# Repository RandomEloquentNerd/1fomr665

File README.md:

# 1form65
These are the design files for my new 65% keyboard PCB, I use Eagle and AutoCAD for designing. 
A few things  before I proceed; as apparent it's in a very crude state currently and needs a lot of tinkering, since this is my first design, I ran into quite a few problems;
1. The board became a tad too crowded, so I made a bit of space on the left for all the electronics to rest, this might make trouble for routing later, but I'm not sure.
2. Since I'll be hand soldering all of the components myself, I went for larger, through hole ones, instead of the usual SMD business. Fitting everything on the board has been a rather nerve wracking affair, but let me know what you think. 
3. Connecting the controller to the matrix. Now this is where I have faltered. Connecting the rows to the controller was straightforward enough, albeit when it comes to connecting columns, the airwire ends up either one key switch down from where I intended (the top pin of the top switch) or on the bottom switch. I figured that the way I had routed the column initially, but on redoing it multiple times, the problem still persists, so I'm uncerrtain how to proceed.

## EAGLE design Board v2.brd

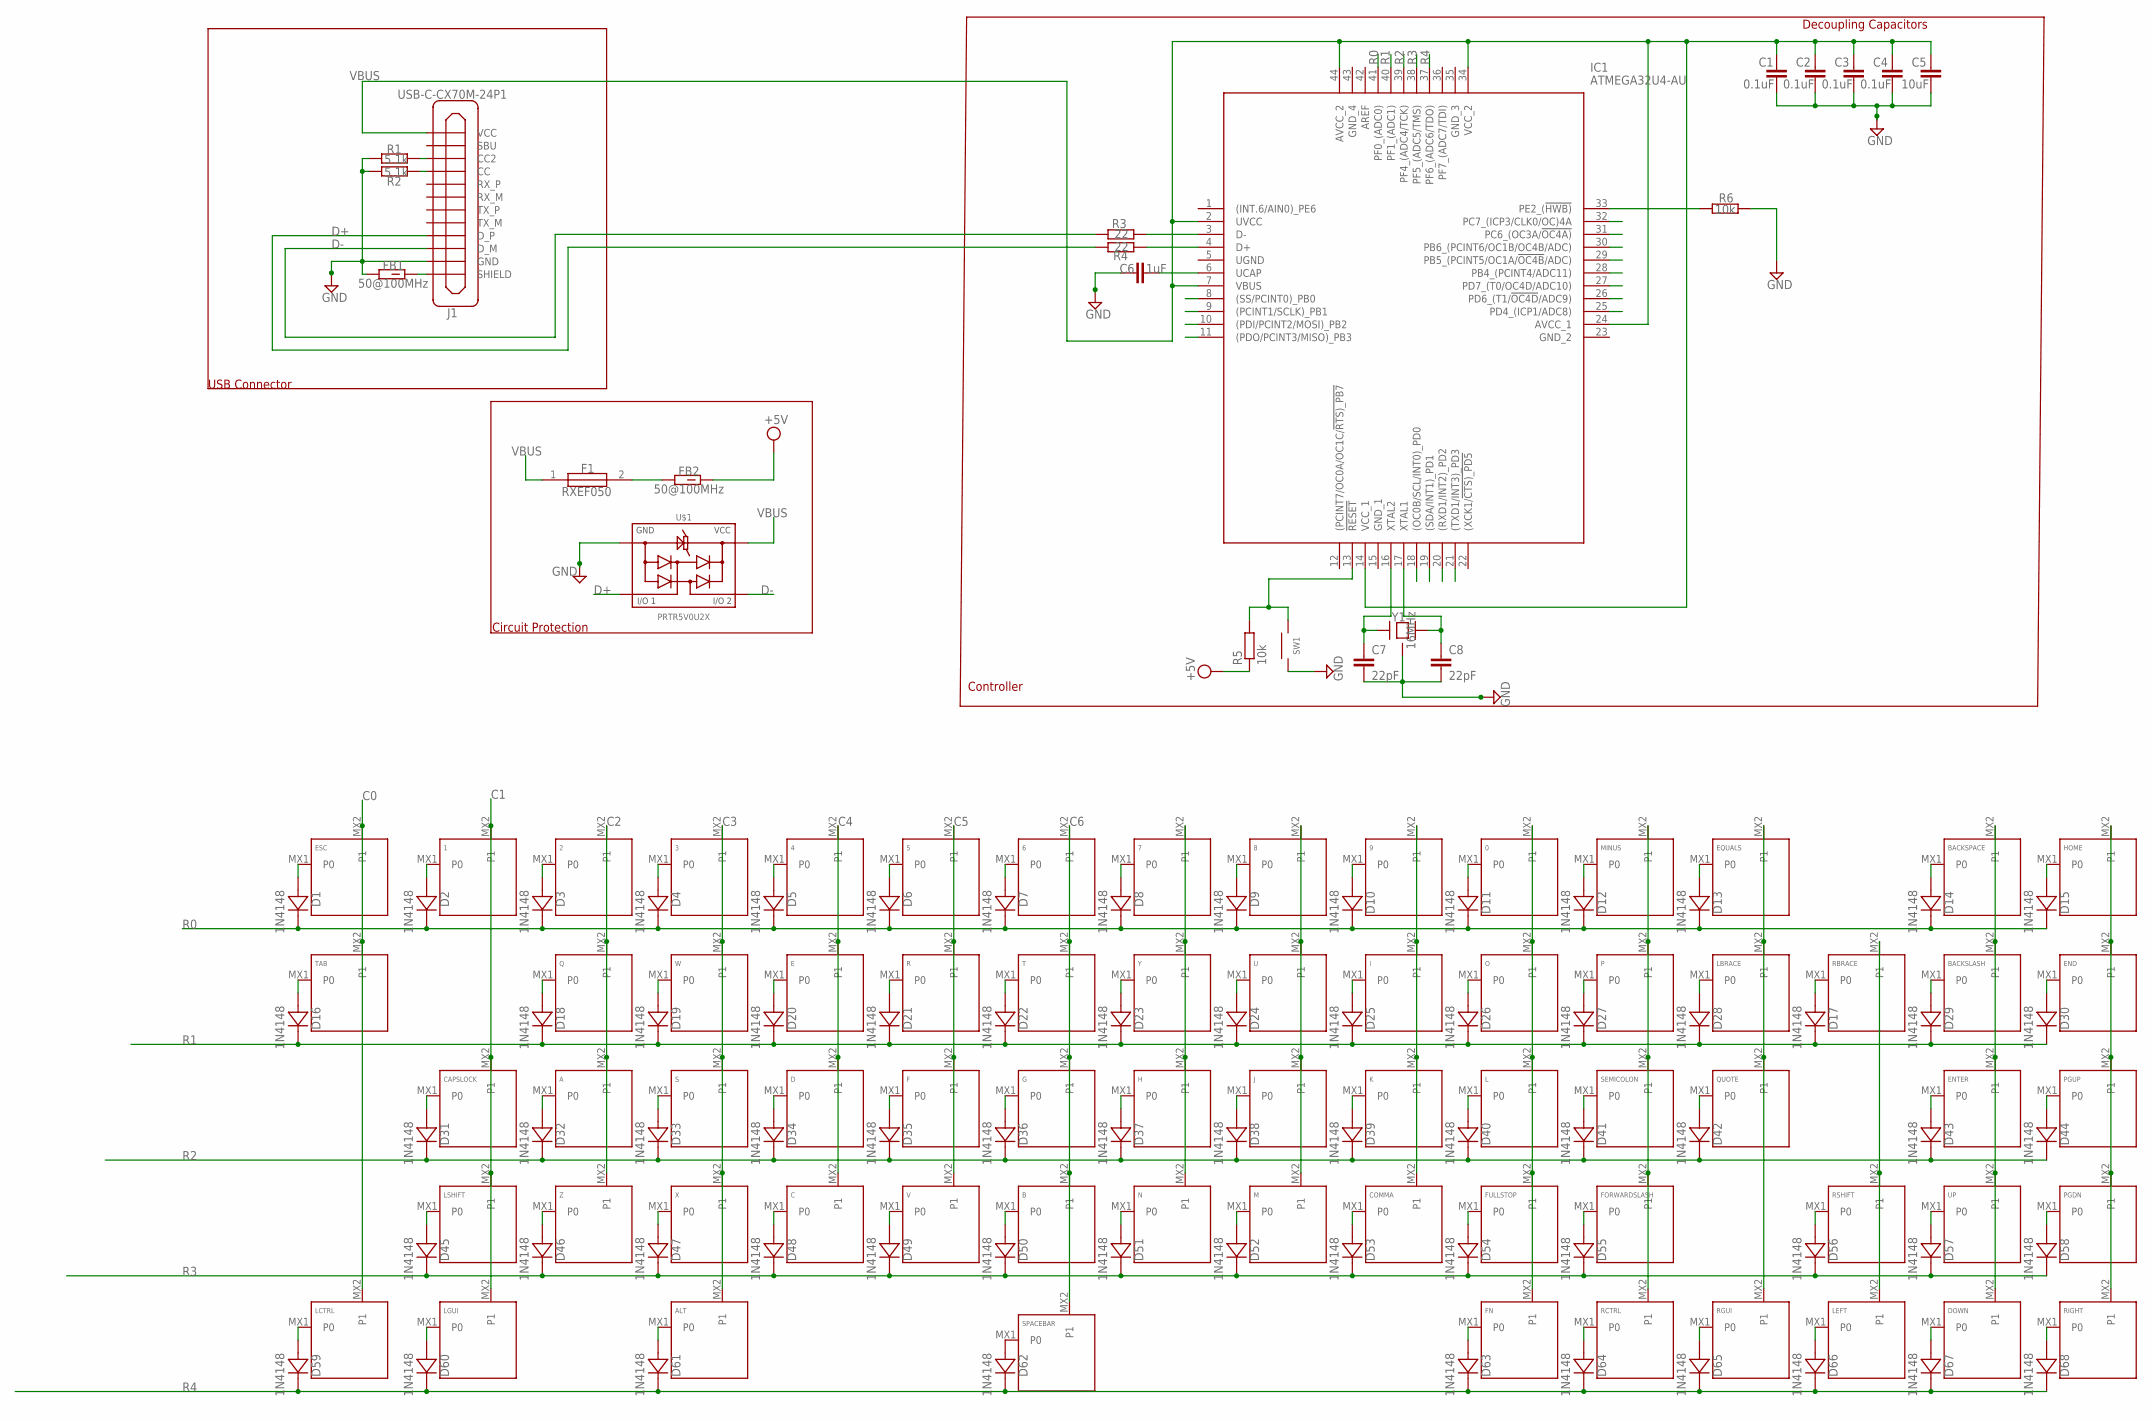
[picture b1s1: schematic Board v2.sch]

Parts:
0, 1, 2, 3, 4, 5, 6, 7, 8, 9: KEYSWITCH-PLAIN-MX-1U; MX-1U
A: KEYSWITCH-PLAIN-MX-1U; MX-1U
ALT: KEYSWITCH-PLAIN-MX-1U; MX-1U
B: KEYSWITCH-PLAIN-MX-1U; MX-1U
BACKSLASH: KEYSWITCH-PLAIN-MX-1U; MX-1U
BACKSPACE: KEYSWITCH-PLAIN-MX-2U; MX-2U
C: KEYSWITCH-PLAIN-MX-1U; MX-1U
C1, C2, C3, C4: 0.1uF; C2.5-3
C5: 10uF; C2.5-3
C6: 1uF; C2.5-3
C7, C8: 22pF; C2.5-3
CAPSLOCK: KEYSWITCH-PLAIN-MX-2U; MX-2U
COMMA: KEYSWITCH-PLAIN-MX-1U; MX-1U
D: KEYSWITCH-PLAIN-MX-1U; MX-1U
D1, D2, D3, D4, D5, D6, D7, D8, D9, D10, D11, D12, D13, D14, D15, D16, D17, D18, D19, D20, D21, D22, D23, D24, D25, D26, D27, D28, D29, D30, D31, D32, D33, D34, D35, D36, D37, D38, D39, D40, D41, D42, D43, D44, D45, D46, D47, D48, D49, D50, D51, D52, D53, D54, D55, D56, D57, D58, D59, D60, D61, D62, D63, D64, D65, D66, D67, D68: 1N4148; DO-35
DOWN: KEYSWITCH-PLAIN-MX-1U; MX-1U
E: KEYSWITCH-PLAIN-MX-1U; MX-1U
END: KEYSWITCH-PLAIN-MX-1U; MX-1U
ENTER: KEYSWITCH-PLAIN-MX-2U; MX-2U
EQUALS: KEYSWITCH-PLAIN-MX-1U; MX-1U
ESC: KEYSWITCH-PLAIN-MX-1U; MX-1U
F: KEYSWITCH-PLAIN-MX-1U; MX-1U
F1: RXEF050
FB1, FB2: 50@100MHz; BEADC3216X130N
FN: KEYSWITCH-PLAIN-MX-1U; MX-1U
FORWARDSLASH: KEYSWITCH-PLAIN-MX-1U; MX-1U
FULLSTOP: KEYSWITCH-PLAIN-MX-1U; MX-1U
G: KEYSWITCH-PLAIN-MX-1U; MX-1U
H: KEYSWITCH-PLAIN-MX-1U; MX-1U
HOME: KEYSWITCH-PLAIN-MX-1U; MX-1U
I: KEYSWITCH-PLAIN-MX-1U; MX-1U
IC1: ATMEGA32U4-AU; QFP80P1200X1200X120-44N
J: KEYSWITCH-PLAIN-MX-1U; MX-1U
J1: USB-C-CX70M-24P1; CX70M-24P1
K: KEYSWITCH-PLAIN-MX-1U; MX-1U
L: KEYSWITCH-PLAIN-MX-1U; MX-1U
LBRACE: KEYSWITCH-PLAIN-MX-1U; MX-1U
LCTRL: KEYSWITCH-PLAIN-MX-1U; MX-1U
LEFT: KEYSWITCH-PLAIN-MX-1U; MX-1U
LGUI: KEYSWITCH-PLAIN-MX-1U; MX-1U
LSHIFT: KEYSWITCH-PLAIN-MX-2U; MX-2U
M: KEYSWITCH-PLAIN-MX-1U; MX-1U
MINUS: KEYSWITCH-PLAIN-MX-1U; MX-1U
N: KEYSWITCH-PLAIN-MX-1U; MX-1U
O: KEYSWITCH-PLAIN-MX-1U; MX-1U
P: KEYSWITCH-PLAIN-MX-1U; MX-1U
PGDN: KEYSWITCH-PLAIN-MX-1U; MX-1U
PGUP: KEYSWITCH-PLAIN-MX-1U; MX-1U
Q: KEYSWITCH-PLAIN-MX-1U; MX-1U
QUOTE: KEYSWITCH-PLAIN-MX-1U; MX-1U
R: KEYSWITCH-PLAIN-MX-1U; MX-1U
R1, R2: 5.1k; THT-RESISTOR-SMALL
R3, R4: 22; THT-RESISTOR-SMALL
R5, R6: 10k; THT-RESISTOR-SMALL
RBRACE: KEYSWITCH-PLAIN-MX-1U; MX-1U
RCTRL: KEYSWITCH-PLAIN-MX-1U; MX-1U
RGUI: KEYSWITCH-PLAIN-MX-1U; MX-1U
RIGHT: KEYSWITCH-PLAIN-MX-1U; MX-1U
RSHIFT: KEYSWITCH-PLAIN-MX-2U; MX-2U
S: KEYSWITCH-PLAIN-MX-1U; MX-1U
SEMICOLON: KEYSWITCH-PLAIN-MX-1U; MX-1U
SPACEBAR: KEYSWITCH-PLAIN-MX-6.25U-FLIPPED; MX-6.25U-FLIPPED
SW1: SWITCH-SMD-EVP-BB2A9B00
T: KEYSWITCH-PLAIN-MX-1U; MX-1U
TAB: KEYSWITCH-PLAIN-MX-1U; MX-1U
U: KEYSWITCH-PLAIN-MX-1U; MX-1U
U$1: PRTR5V0U2X
UP: KEYSWITCH-PLAIN-MX-1U; MX-1U
V: KEYSWITCH-PLAIN-MX-1U; MX-1U
W: KEYSWITCH-PLAIN-MX-1U; MX-1U
X: KEYSWITCH-PLAIN-MX-1U; MX-1U
Y: KEYSWITCH-PLAIN-MX-1U; MX-1U
Y1: 16MHz; CRYSTAL-3.2X2.5
Z: KEYSWITCH-PLAIN-MX-1U; MX-1U

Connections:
C0: ESC.MX2 (P1), IC1.8 ((SS/PCINT0)_PB0), LCTRL.MX2 (P1), TAB.MX2 (P1)
C1: 1.MX2 (P1), CAPSLOCK.MX2 (P1), LGUI.MX2 (P1), LSHIFT.MX2 (P1)
C2: 2.MX2 (P1), A.MX2 (P1), Q.MX2 (P1), Z.MX2 (P1)
C3: 3.MX2 (P1), ALT.MX2 (P1), S.MX2 (P1), W.MX2 (P1), X.MX2 (P1)
C4: 4.MX2 (P1), C.MX2 (P1), D.MX2 (P1), E.MX2 (P1)
C5: 5.MX2 (P1), F.MX2 (P1), R.MX2 (P1), V.MX2 (P1)
C6: 6.MX2 (P1), B.MX2 (P1), G.MX2 (P1), SPACEBAR.MX2 (P1), T.MX2 (P1)
C7: 7.MX2 (P1), H.MX2 (P1), N.MX2 (P1), Y.MX2 (P1)
C8: 8.MX2 (P1), J.MX2 (P1), M.MX2 (P1), U.MX2 (P1)
C9: 9.MX2 (P1), COMMA.MX2 (P1), I.MX2 (P1), K.MX2 (P1)
C10: 0.MX2 (P1), FN.MX2 (P1), FULLSTOP.MX2 (P1), L.MX2 (P1), O.MX2 (P1)
C11: FORWARDSLASH.MX2 (P1), MINUS.MX2 (P1), P.MX2 (P1), RCTRL.MX2 (P1), SEMICOLON.MX2 (P1)
C12: EQUALS.MX2 (P1), LBRACE.MX2 (P1), QUOTE.MX2 (P1), RGUI.MX2 (P1)
C13: LEFT.MX2 (P1), RBRACE.MX2 (P1), RSHIFT.MX2 (P1)
C14: BACKSLASH.MX2 (P1), BACKSPACE.MX2 (P1), DOWN.MX2 (P1), ENTER.MX2 (P1), UP.MX2 (P1)
C15: END.MX2 (P1), HOME.MX2 (P1), PGDN.MX2 (P1), PGUP.MX2 (P1), RIGHT.MX2 (P1)
D+: J1.A6 (D_P), J1.B6 (D_P), R4.A1 (1), R4.A2 (1), R4.A3 (1), U$1.2
D-: J1.A7 (D_M), J1.B7 (D_M), R3.A1 (1), R3.A2 (1), R3.A3 (1), U$1.3
GND: C1.2, C2.2, C3.2, C4.2, C5.2, C6.1, C7.2, C8.2, FB1.1, J1.A1 (GND), J1.A12 (GND), J1.B1 (GND), J1.B12 (GND), R1.A1 (1), R1.A2 (1), R1.A3 (1), R2.A1 (1), R2.A2 (1), R2.A3 (1), R6.B1 (2), R6.B2 (2), R6.B3 (2), SW1.A@1 (1), SW1.A@2 (1), U$1.1, Y1.2 (GND), Y1.4 (GND)
unnamed: D1.A, ESC.MX1 (P0)
unnamed: 1.MX1 (P0), D2.A
unnamed: 2.MX1 (P0), D3.A
unnamed: 3.MX1 (P0), D4.A
unnamed: 4.MX1 (P0), D5.A
unnamed: 5.MX1 (P0), D6.A
unnamed: 6.MX1 (P0), D7.A
unnamed: 7.MX1 (P0), D8.A
unnamed: 8.MX1 (P0), D9.A
unnamed: 9.MX1 (P0), D10.A
unnamed: 0.MX1 (P0), D11.A
unnamed: D12.A, MINUS.MX1 (P0)
unnamed: D13.A, EQUALS.MX1 (P0)
unnamed: BACKSPACE.MX1 (P0), D14.A
unnamed: D15.A, HOME.MX1 (P0)
unnamed: D16.A, TAB.MX1 (P0)
unnamed: D18.A, Q.MX1 (P0)
unnamed: D19.A, W.MX1 (P0)
unnamed: D20.A, E.MX1 (P0)
unnamed: D21.A, R.MX1 (P0)
unnamed: D22.A, T.MX1 (P0)
unnamed: D23.A, Y.MX1 (P0)
unnamed: D24.A, U.MX1 (P0)
unnamed: D25.A, I.MX1 (P0)
unnamed: D26.A, O.MX1 (P0)
unnamed: D27.A, P.MX1 (P0)
unnamed: D28.A, LBRACE.MX1 (P0)
unnamed: BACKSLASH.MX1 (P0), D29.A
unnamed: D30.A, END.MX1 (P0)
unnamed: CAPSLOCK.MX1 (P0), D31.A
unnamed: A.MX1 (P0), D32.A
unnamed: D33.A, S.MX1 (P0)
unnamed: D.MX1 (P0), D34.A
unnamed: D35.A, F.MX1 (P0)
unnamed: D36.A, G.MX1 (P0)
unnamed: D37.A, H.MX1 (P0)
unnamed: D38.A, J.MX1 (P0)
unnamed: D39.A, K.MX1 (P0)
unnamed: D40.A, L.MX1 (P0)
unnamed: D41.A, SEMICOLON.MX1 (P0)
unnamed: D42.A, QUOTE.MX1 (P0)
unnamed: D43.A, ENTER.MX1 (P0)
unnamed: D44.A, PGUP.MX1 (P0)
unnamed: D45.A, LSHIFT.MX1 (P0)
unnamed: D46.A, Z.MX1 (P0)
unnamed: D47.A, X.MX1 (P0)
unnamed: C.MX1 (P0), D48.A
unnamed: D49.A, V.MX1 (P0)
unnamed: B.MX1 (P0), D50.A
unnamed: D51.A, N.MX1 (P0)
unnamed: D52.A, M.MX1 (P0)
unnamed: COMMA.MX1 (P0), D53.A
unnamed: D54.A, FULLSTOP.MX1 (P0)
unnamed: D55.A, FORWARDSLASH.MX1 (P0)
unnamed: D57.A, UP.MX1 (P0)
unnamed: D58.A, PGDN.MX1 (P0)
unnamed: D56.A, RSHIFT.MX1 (P0)
unnamed: D59.A, LCTRL.MX1 (P0)
unnamed: D60.A, LGUI.MX1 (P0)
unnamed: ALT.MX1 (P0), D61.A
unnamed: D62.A, SPACEBAR.MX1 (P0)
unnamed: D63.A, FN.MX1 (P0)
unnamed: D64.A, RCTRL.MX1 (P0)
unnamed: D65.A, RGUI.MX1 (P0)
unnamed: D66.A, LEFT.MX1 (P0)
unnamed: D67.A, DOWN.MX1 (P0)
unnamed: D68.A, RIGHT.MX1 (P0)
unnamed: D17.A, RBRACE.MX1 (P0)
unnamed: F1.2, FB2.1
unnamed: J1.B5 (CC2), R1.B1 (2), R1.B2 (2), R1.B3 (2)
unnamed: J1.A5 (CC), R2.B1 (2), R2.B2 (2), R2.B3 (2)
unnamed: C6.2, IC1.6 (UCAP)
unnamed: C7.1, IC1.16 (XTAL2), Y1.1
unnamed: FB1.2, J1.SHIELD@1 (SHIELD), J1.SHIELD@2 (SHIELD), J1.SHIELD@3 (SHIELD), J1.SHIELD@4 (SHIELD)
unnamed: IC1.3 (D-), R3.B1 (2), R3.B2 (2), R3.B3 (2)
unnamed: IC1.4 (D+), R4.B1 (2), R4.B2 (2), R4.B3 (2)
unnamed: C8.1, IC1.17 (XTAL1), Y1.3 (2)
unnamed: IC1.13 (!RESET), R5.B1 (2), R5.B2 (2), R5.B3 (2), SW1.B@3 (2), SW1.B@4 (2)
unnamed: IC1.33 (PE2_(!HWB)), R6.A1 (1), R6.A2 (1), R6.A3 (1)
R0: D1.C, D2.C, D3.C, D4.C, D5.C, D6.C, D7.C, D8.C, D9.C, D10.C, D11.C, D12.C, D13.C, D14.C, D15.C, IC1.41 (PF0_(ADC0))
R1: D16.C, D17.C, D18.C, D19.C, D20.C, D21.C, D22.C, D23.C, D24.C, D25.C, D26.C, D27.C, D28.C, D29.C, D30.C, IC1.40 (PF1_(ADC1))
R2: D31.C, D32.C, D33.C, D34.C, D35.C, D36.C, D37.C, D38.C, D39.C, D40.C, D41.C, D42.C, D43.C, D44.C, IC1.39 (PF4_(ADC4/TCK))
R3: D45.C, D46.C, D47.C, D48.C, D49.C, D50.C, D51.C, D52.C, D53.C, D54.C, D55.C, D56.C, D57.C, D58.C, IC1.38 (PF5_(ADC5/TMS))
R4: D59.C, D60.C, D61.C, D62.C, D63.C, D64.C, D65.C, D66.C, D67.C, D68.C, IC1.37 (PF6_(ADC6/TDO))
VBUS: C1.1, C2.1, C3.1, C4.1, C5.1, F1.1, IC1.2 (UVCC), IC1.7 (VBUS), IC1.14 (VCC_1), IC1.24 (AVCC_1), IC1.34 (VCC_2), IC1.44 (AVCC_2), J1.A4 (VCC), J1.A9 (VCC), J1.B4 (VCC), J1.B9 (VCC), U$1.4
VCC: FB2.2, R5.A1 (1), R5.A2 (1), R5.A3 (1)

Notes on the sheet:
Controller
Decoupling Capacitors
USB Connector
Circuit Protection

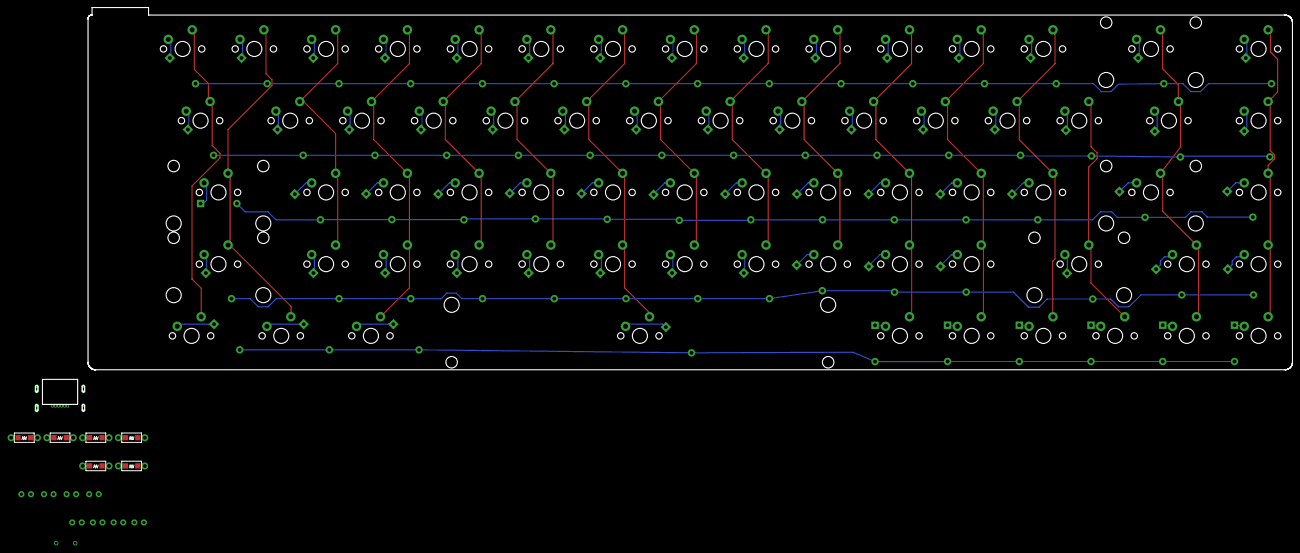
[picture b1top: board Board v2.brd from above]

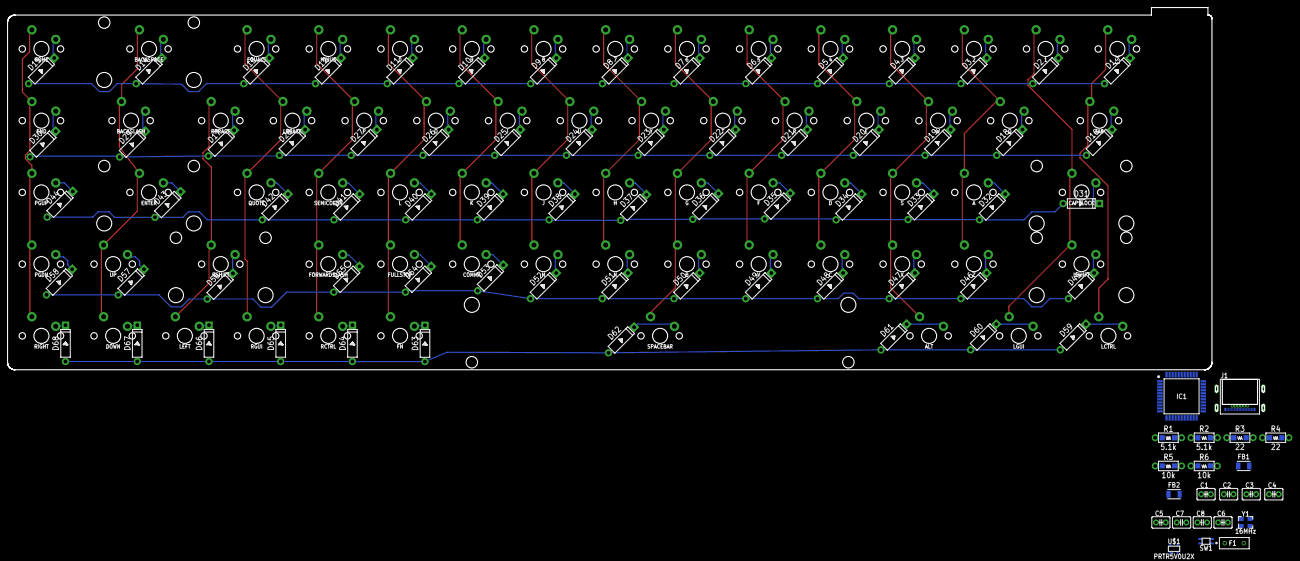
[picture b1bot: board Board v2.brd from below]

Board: 2 copper layers, 319.9 x 96.2 mm, 158 parts (90 on the bottom side), 105 nets.
